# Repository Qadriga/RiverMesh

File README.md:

# RiverMesh
ESP32-S3 based pcb node for Mesh networking

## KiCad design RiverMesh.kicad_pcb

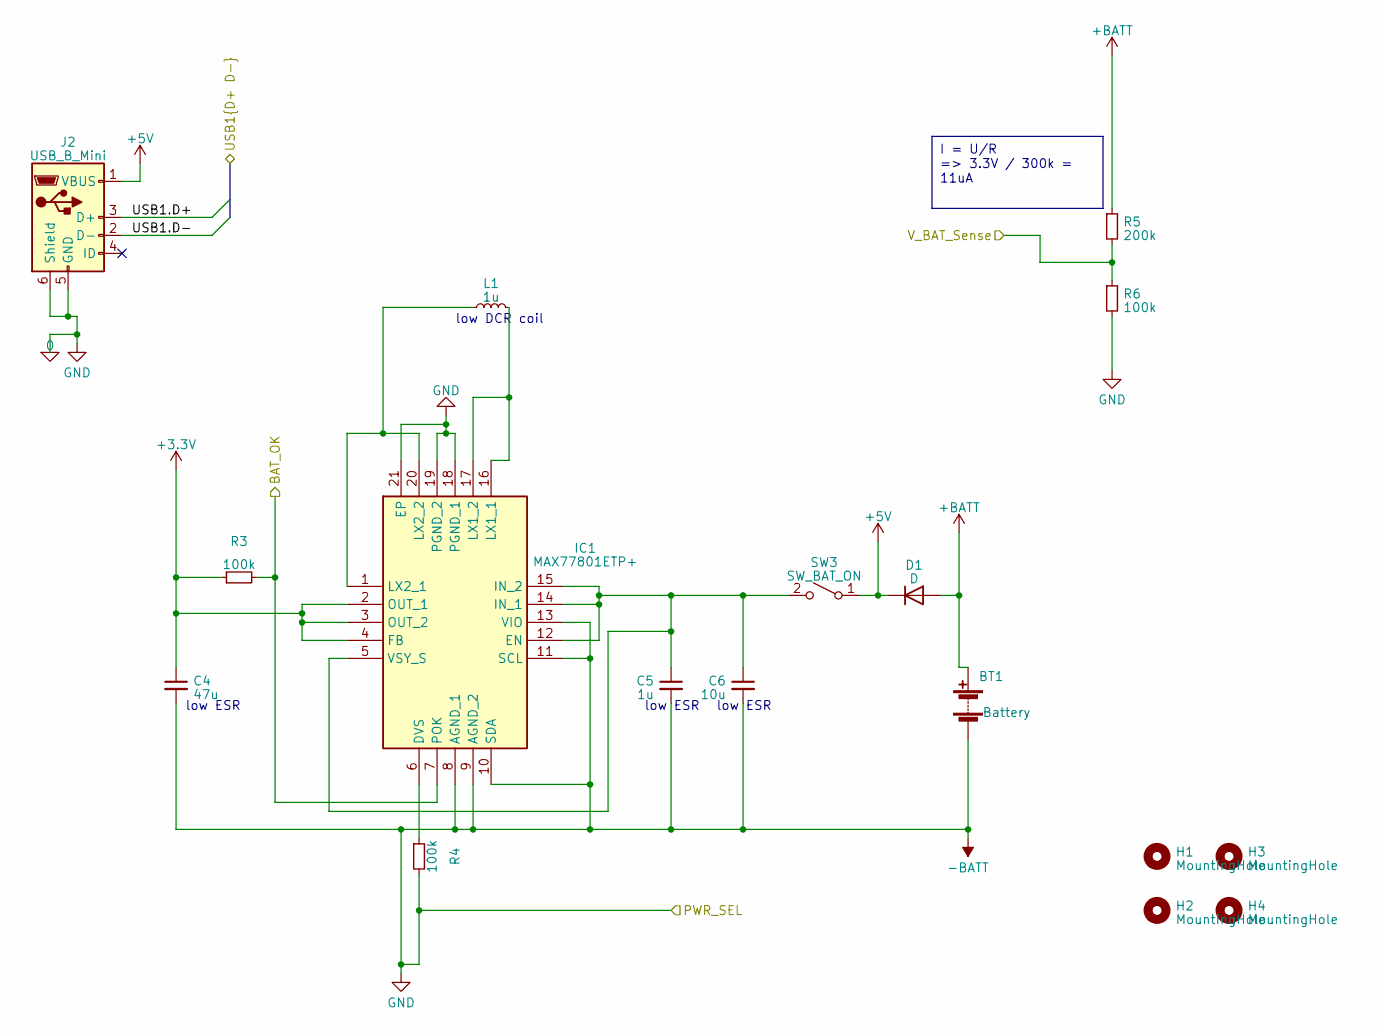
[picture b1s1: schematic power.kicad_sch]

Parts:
BT1: Battery; TE_440055-2_1x02_P2.00mm_Horizontal
C4: 47u; C_0805_2012Metric_Pad1.18x1.45mm_HandSolder
C5: 1u; C_0805_2012Metric_Pad1.18x1.45mm_HandSolder
C6: 10u; C_0805_2012Metric_Pad1.18x1.45mm_HandSolder
D1: D; D_SOD-323_HandSoldering
H1, H2, H3, H4: MountingHole; MountingHole_2.2mm_M2
IC1: MAX77801ETP+; QFN50P400X400X80-21N; Mouser Part Number 700-MAX77801ETP+
J2: USB_B_Mini; USB_Mini-B_Wuerth_65100516121_Horizontal
L1: 1u; L_0805_2012Metric_Pad1.15x1.40mm_HandSolder
R3, R4, R6: 100k; R_0805_2012Metric_Pad1.20x1.40mm_HandSolder
R5: 200k; R_0805_2012Metric_Pad1.20x1.40mm_HandSolder
SW3: SW_BAT_ON; SW_E-Switch_EG1271_SPDT

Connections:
+3.3V: C4.1, IC1.2 (OUT_1), IC1.3 (OUT_2), IC1.4 (FB), R3.1; also elsewhere on the board
+5V: D1.1 (K), J2.1 (VBUS), SW3.1 (A)
+BATT: BT1.1 (+), D1.2 (A), R5.1
-BATT: BT1.2 (-), C4.2, C5.2, C6.2, IC1.8 (AGND_1), IC1.9 (AGND_2), IC1.10 (SDA), IC1.11 (SCL), IC1.13 (VIO), IC1.18 (PGND_1), IC1.19 (PGND_2), IC1.21 (EP), J2.5 (GND), J2.6 (Shield), R4.2, R6.2; also elsewhere on the board
/ESP_MCU/BAT_OK: IC1.7 (POK), R3.2; also elsewhere on the board
/ESP_MCU/USB1.D+: J2.3 (D+); also elsewhere on the board
/ESP_MCU/USB1.D-: J2.2 (D-); also elsewhere on the board
/ESP_MCU/V_SENSE: R5.2, R6.1; also elsewhere on the board
unnamed: IC1.6 (DVS), R4.1
unnamed: C5.1, C6.1, IC1.5 (VSY_S), IC1.12 (EN), IC1.14 (IN_1), IC1.15 (IN_2), SW3.2 (B)
unnamed: IC1.16 (LX1_1), IC1.17 (LX1_2), L1.2
unnamed: IC1.1 (LX2_1), IC1.20 (LX2_2), L1.1

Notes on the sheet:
I = U/R => 3.3V / 300k = 11uA
low ESR
low DCR coil

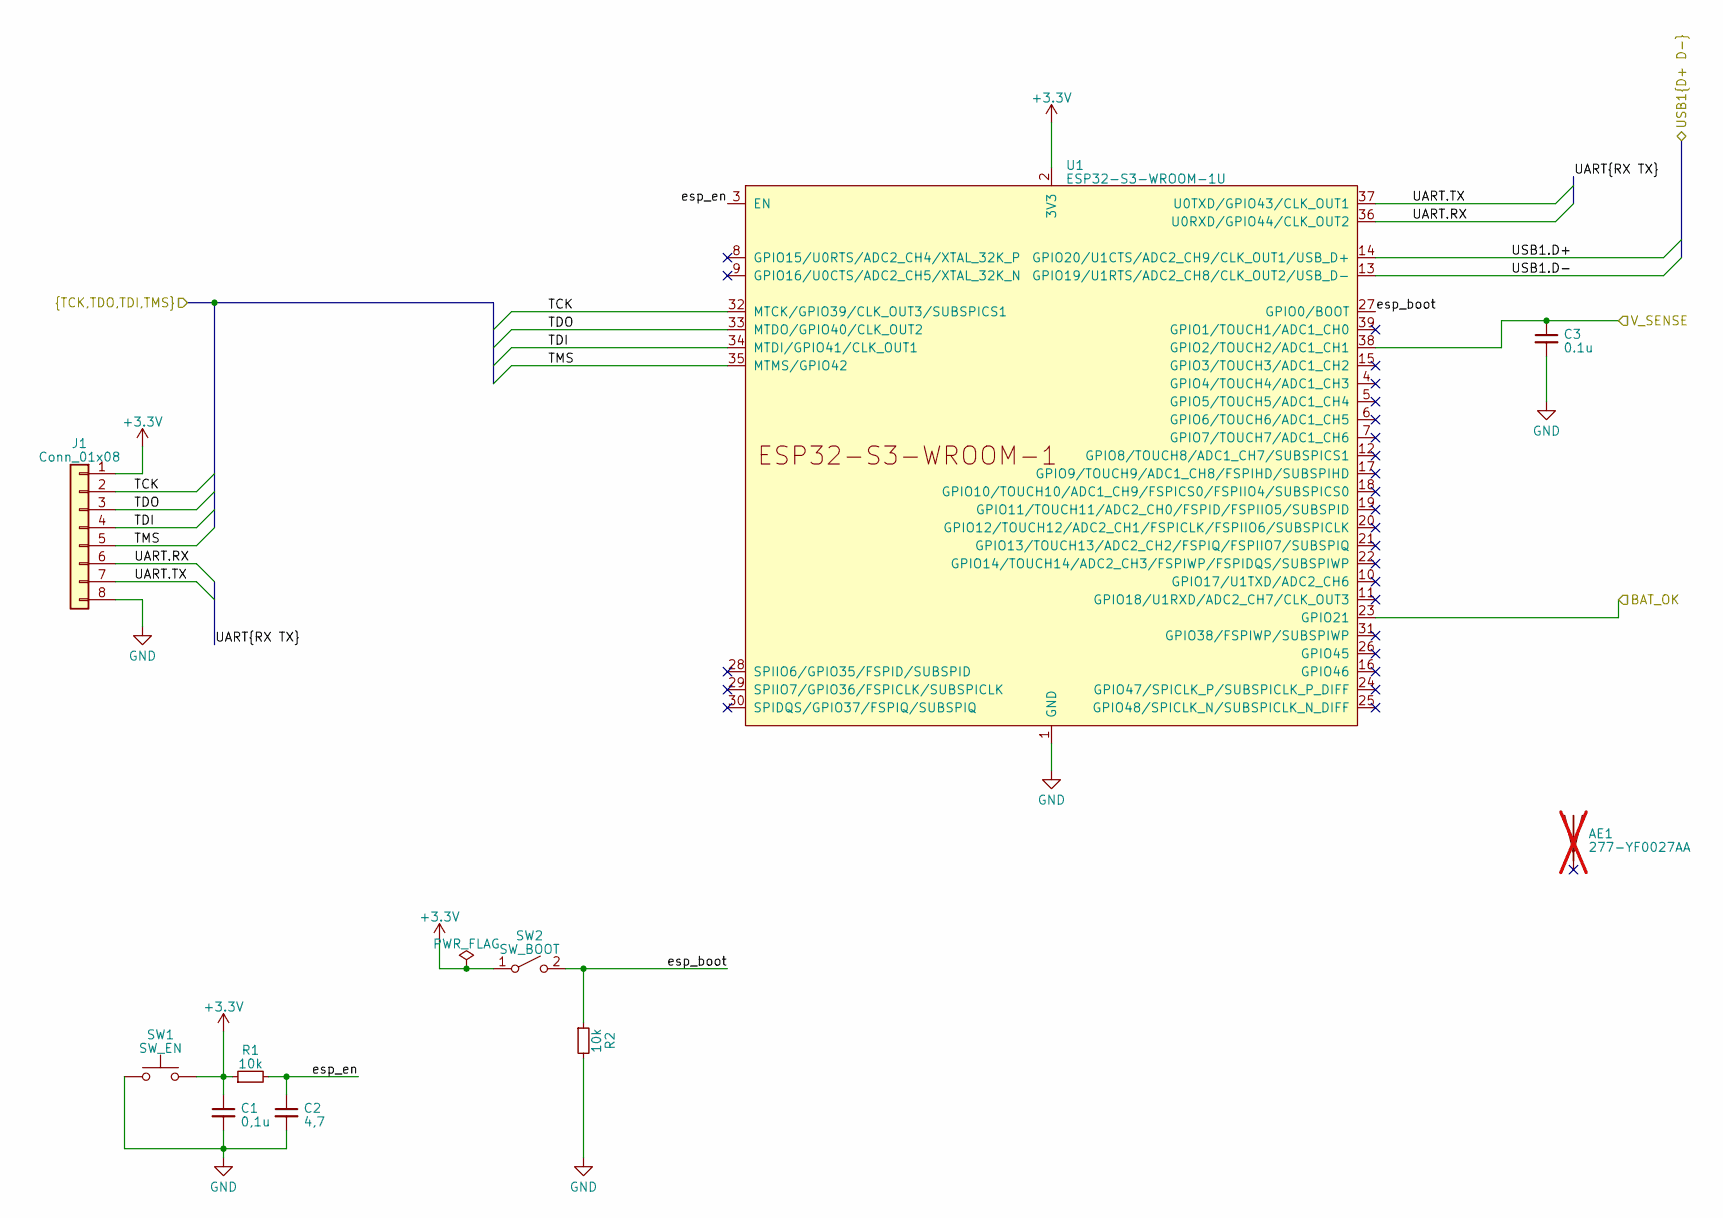
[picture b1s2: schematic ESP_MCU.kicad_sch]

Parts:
AE1: 277-YF0027AA; not fitted
C1: 0,1u; C_0805_2012Metric_Pad1.18x1.45mm_HandSolder
C2: 4,7; C_0805_2012Metric_Pad1.18x1.45mm_HandSolder
C3: 0.1u; C_0805_2012Metric_Pad1.18x1.45mm_HandSolder
J1: Conn_01x08; PinHeader_1x08_P1.27mm_Vertical
R1, R2: 10k; R_0805_2012Metric_Pad1.20x1.40mm_HandSolder
SW1: SW_EN; SW_Push_1P1T-MP_NO_Horizontal_Alps_SKRTLAE010
SW2: SW_BOOT; SW_Push_1P1T-MP_NO_Horizontal_Alps_SKRTLAE010
U1: ESP32-S3-WROOM-1U

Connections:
+3.3V: C1.1, J1.1, R1.1, SW1.2, SW2.1 (A), U1.2 (3V3); also elsewhere on the board
-BATT: C1.2, C2.2, C3.2, J1.8, R2.2, SW1.1, U1.1 (GND), U1.40 (GND), U1.41 (GND); also elsewhere on the board
/ESP_MCU/BAT_OK: U1.23 (GPIO21); also elsewhere on the board
/ESP_MCU/TCK: J1.2, U1.32 (MTCK/GPIO39/CLK_OUT3/SUBSPICS1)
/ESP_MCU/TDI: J1.4, U1.34 (MTDI/GPIO41/CLK_OUT1)
/ESP_MCU/TDO: J1.3, U1.33 (MTDO/GPIO40/CLK_OUT2)
/ESP_MCU/TMS: J1.5, U1.35 (MTMS/GPIO42)
/ESP_MCU/UART.RX: J1.6, U1.36 (U0RXD/GPIO44/CLK_OUT2)
/ESP_MCU/UART.TX: J1.7, U1.37 (U0TXD/GPIO43/CLK_OUT1)
/ESP_MCU/USB1.D+: U1.14 (GPIO20/U1CTS/ADC2_CH9/CLK_OUT1/USB_D+); also elsewhere on the board
/ESP_MCU/USB1.D-: U1.13 (GPIO19/U1RTS/ADC2_CH8/CLK_OUT2/USB_D-); also elsewhere on the board
/ESP_MCU/V_SENSE: C3.1, U1.38 (GPIO2/TOUCH2/ADC1_CH1); also elsewhere on the board
/ESP_MCU/esp_boot: R2.1, SW2.2 (B), U1.27 (GPIO0/BOOT)
/ESP_MCU/esp_en: C2.1, R1.2, U1.3 (EN)

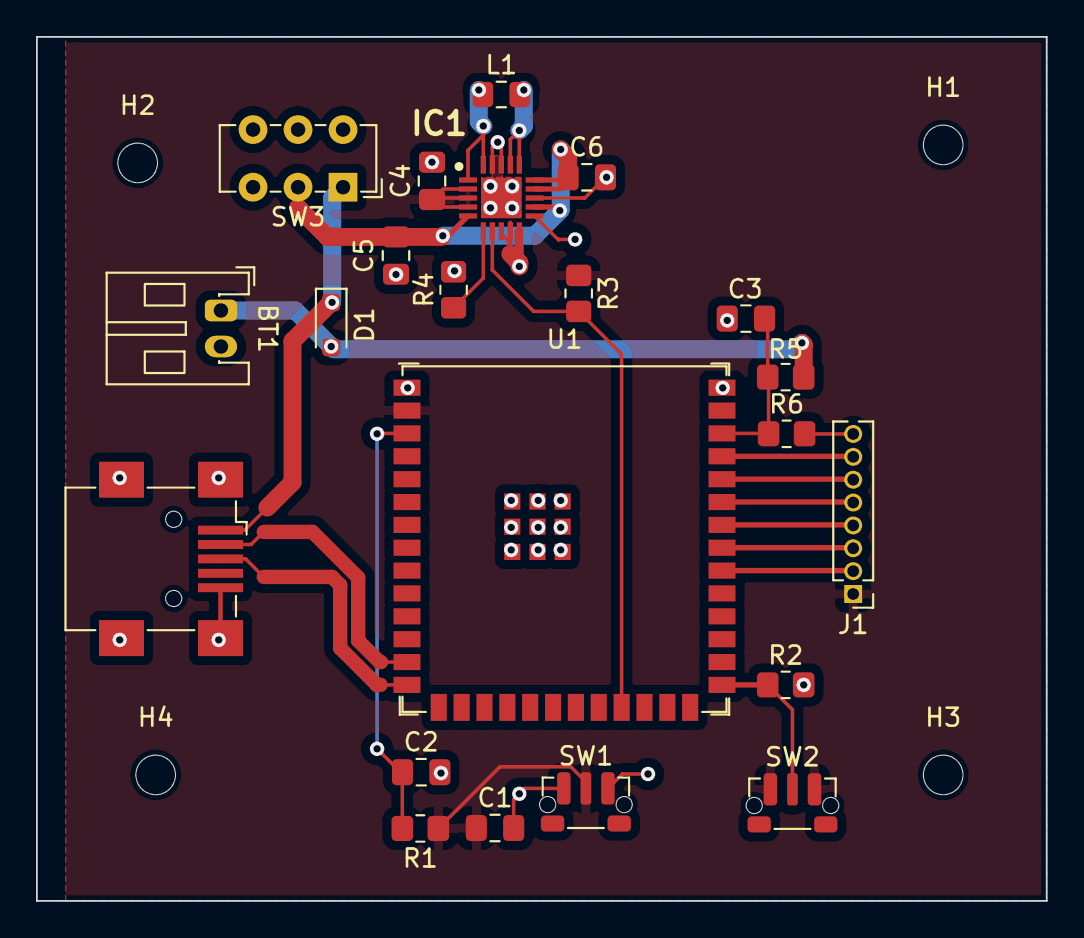
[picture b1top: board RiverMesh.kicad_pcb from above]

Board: 2 copper layers, 56.1 x 48.0 mm, 26 parts (0 on the bottom side), 20 nets.

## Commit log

2023-06-09 finalize routing and shematic
2023-06-09 added esp kicad libaray as submodule
